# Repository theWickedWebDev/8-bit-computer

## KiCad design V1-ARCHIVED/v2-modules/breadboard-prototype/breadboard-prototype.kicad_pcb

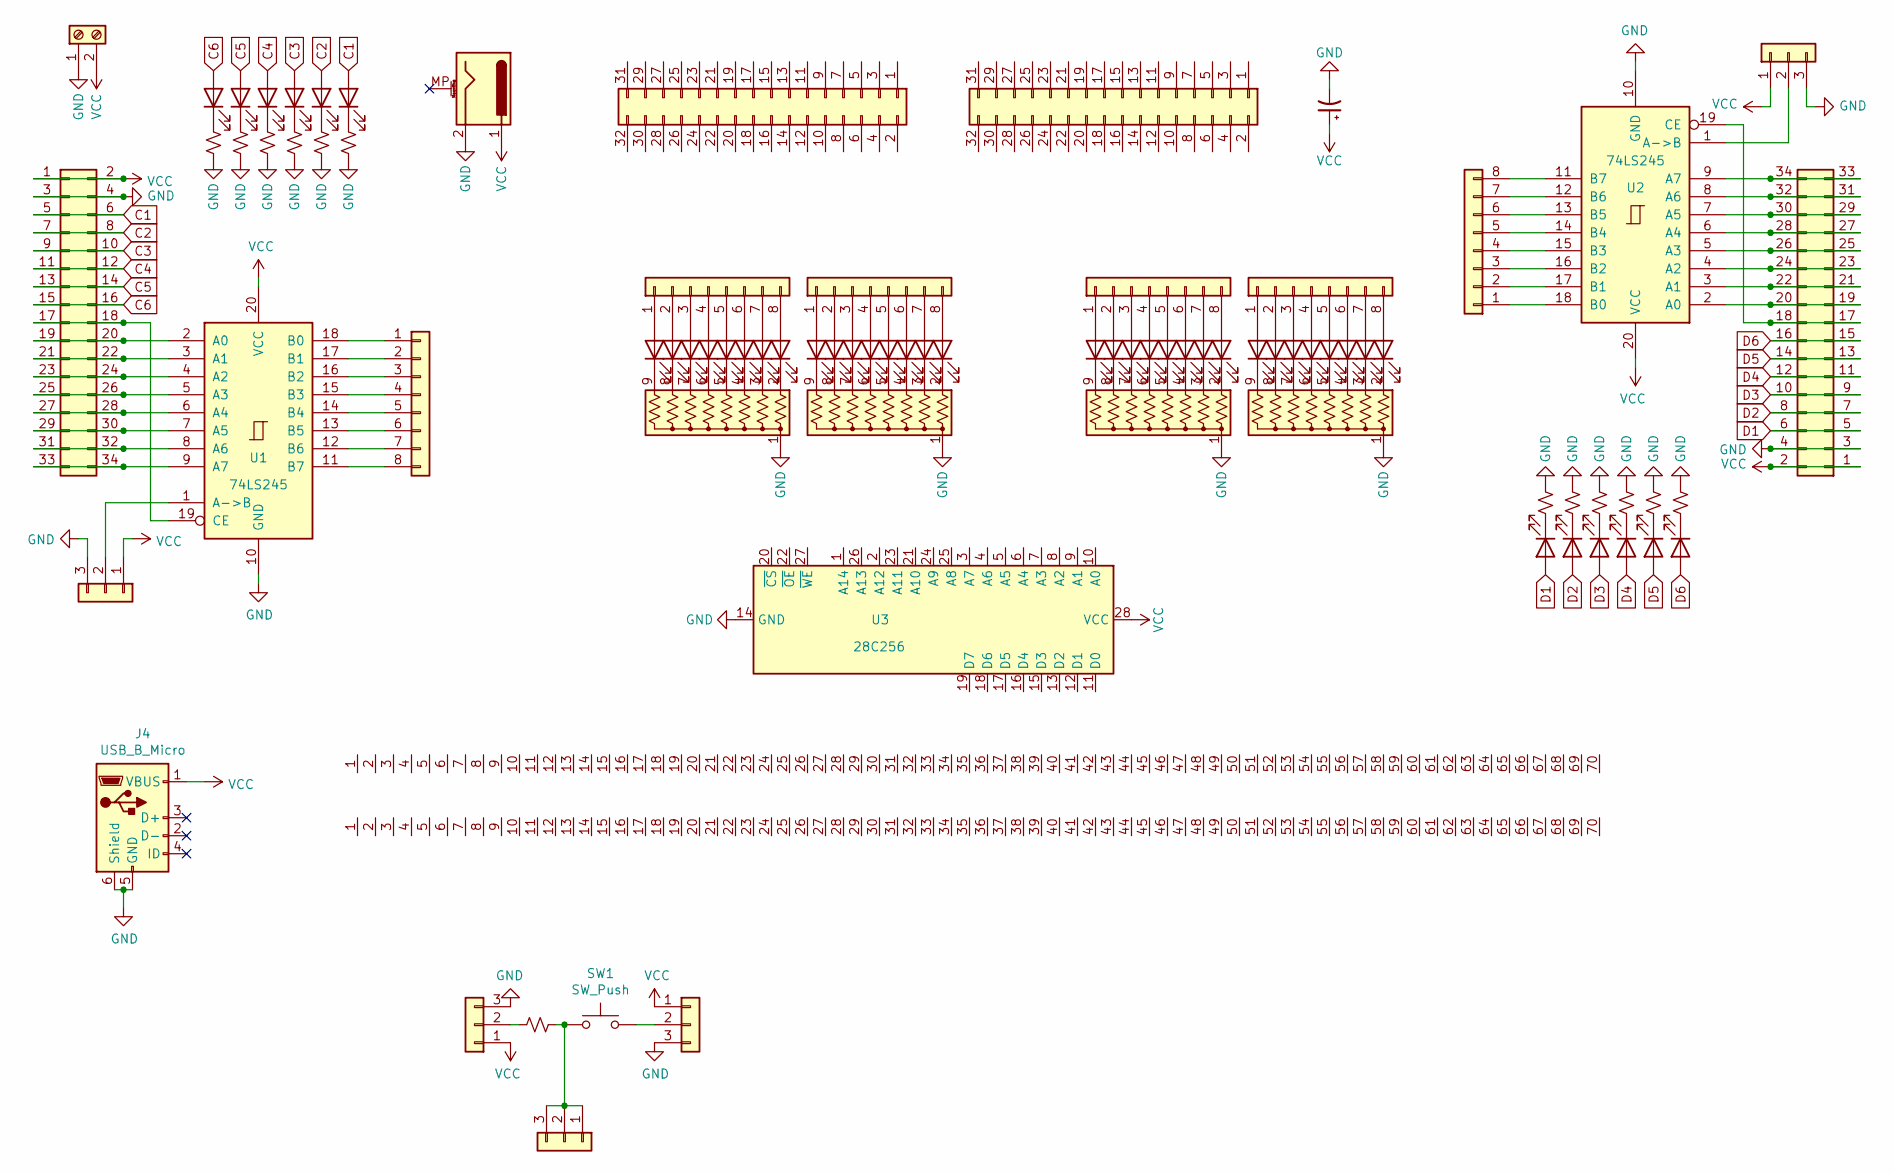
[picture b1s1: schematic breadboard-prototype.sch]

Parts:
C1: CP1_Small; CP_Radial_D8.0mm_P3.50mm
D1, D2, D3, D4, D5, D7, D8, D9, D10, D11, D12: LED; LED_0805_2012Metric
D6: LED; LED_1206_3216Metric
D13, D14, D15, D16, D17, D18, D19, D20, D21, D22, D23, D24, D25, D26, D27, D28, D29, D30, D31, D32, D33, D34, D35, D36, D37, D38, D39, D40, D41, D42, D43, D44: LED; LED_D3.0mm
J1, J6: Conn_02x17_Odd_Even; PinHeader_2x17_P2.54mm_Vertical
J2, J7, J18, J19, J20: Conn_01x03; PinHeader_1x03_P2.54mm_Vertical
J3, J8, J12, J13, J15, J16: Conn_01x08; PinHeader_1x08_P2.54mm_Vertical
J4: USB_B_Micro; USB_Micro-B_Wuerth_629105150521_CircularHoles
J5: Screw_Terminal_01x02; TerminalBlock_Phoenix_MKDS-1,5-2_1x02_P5.00mm_Horizontal
J9, J10: Conn_02x16_Odd_Even; connector_16_2
J11, J14: Conn_01x01; line_6x70
J17: Barrel_Jack_MountingPin; BarrelJack_Horizontal
R1, R2, R3, R4, R5, R6: R_Small_US; R_1206_3216Metric
R9, R10, R11, R12, R13, R14, R29: R_Small_US; R_0805_2012Metric
RN1, RN2, RN3, RN4: R_Network08_US; R_Array_SIP9
SW1: SW_Push; SW_PUSH_6mm
U1, U2: 74LS245; DIP-20_W7.62mm
U3: 28C256

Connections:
C1: D1.2 (A), J1.5, J1.6
C2: D2.2 (A), J1.7, J1.8
C3: D3.2 (A), J1.9, J1.10
C4: D4.2 (A), J1.11, J1.12
C5: D5.2 (A), J1.13, J1.14
C6: D6.2 (A), J1.15, J1.16
D1: D12.2 (A), J6.5, J6.6
D2: D11.2 (A), J6.7, J6.8
D3: D10.2 (A), J6.9, J6.10
D4: D9.2 (A), J6.11, J6.12
D5: D8.2 (A), J6.13, J6.14
D6: D7.2 (A), J6.15, J6.16
GND: C1.2, J1.3, J1.4, J2.3, J4.5 (GND), J4.6 (Shield), J5.1, J6.3, J6.4, J7.3, J17.2, J18.3, J19.3, R1.2, R2.2, R3.2, R4.2, R5.2, R6.2, R9.2, R10.2, R11.2, R12.2, R13.2, R14.2, RN1.1 (common), RN2.1 (common), RN3.1 (common), RN4.1 (common), U1.10 (GND), U2.10 (GND), U3.14 (GND)
unnamed: D1.1 (K), R1.1
unnamed: D2.1 (K), R2.1
unnamed: D3.1 (K), R3.1
unnamed: D4.1 (K), R4.1
unnamed: D5.1 (K), R5.1
unnamed: D6.1 (K), R6.1
unnamed: D7.1 (K), R9.1
unnamed: D8.1 (K), R10.1
unnamed: D9.1 (K), R11.1
unnamed: D10.1 (K), R12.1
unnamed: D11.1 (K), R13.1
unnamed: D12.1 (K), R14.1
unnamed: D13.1 (K), RN3.9 (R8)
unnamed: D13.2 (A), J12.1
unnamed: D14.1 (K), RN3.8 (R7)
unnamed: D14.2 (A), J12.2
unnamed: D15.1 (K), RN3.7 (R6)
unnamed: D15.2 (A), J12.3
unnamed: D16.1 (K), RN3.6 (R5)
unnamed: D16.2 (A), J12.4
unnamed: D17.1 (K), RN3.5 (R4)
unnamed: D17.2 (A), J12.5
unnamed: D18.1 (K), RN3.4 (R3)
unnamed: D18.2 (A), J12.6
unnamed: D19.1 (K), RN3.3 (R2)
unnamed: D19.2 (A), J12.7
unnamed: D20.1 (K), RN3.2 (R1)
unnamed: D20.2 (A), J12.8
unnamed: D21.1 (K), RN4.9 (R8)
unnamed: D21.2 (A), J13.1
unnamed: D22.1 (K), RN4.8 (R7)
unnamed: D22.2 (A), J13.2
unnamed: D23.1 (K), RN4.7 (R6)
unnamed: D23.2 (A), J13.3
unnamed: D24.1 (K), RN4.6 (R5)
unnamed: D24.2 (A), J13.4
unnamed: D25.1 (K), RN4.5 (R4)
unnamed: D25.2 (A), J13.5
unnamed: D26.1 (K), RN4.4 (R3)
unnamed: D26.2 (A), J13.6
unnamed: D27.1 (K), RN4.3 (R2)
unnamed: D27.2 (A), J13.7
unnamed: D28.1 (K), RN4.2 (R1)
unnamed: D28.2 (A), J13.8
unnamed: D29.1 (K), RN1.9 (R8)
unnamed: D29.2 (A), J15.1
unnamed: D30.1 (K), RN1.8 (R7)
unnamed: D30.2 (A), J15.2
unnamed: D31.1 (K), RN1.7 (R6)
unnamed: D31.2 (A), J15.3
unnamed: D32.1 (K), RN1.6 (R5)
unnamed: D32.2 (A), J15.4
unnamed: D33.1 (K), RN1.5 (R4)
unnamed: D33.2 (A), J15.5
unnamed: D34.1 (K), RN1.4 (R3)
unnamed: D34.2 (A), J15.6
unnamed: D35.1 (K), RN1.3 (R2)
unnamed: D35.2 (A), J15.7
unnamed: D36.1 (K), RN1.2 (R1)
unnamed: D36.2 (A), J15.8
unnamed: D37.1 (K), RN2.9 (R8)
unnamed: D37.2 (A), J16.1
unnamed: D38.1 (K), RN2.8 (R7)
unnamed: D38.2 (A), J16.2
unnamed: D39.1 (K), RN2.7 (R6)
unnamed: D39.2 (A), J16.3
unnamed: D40.1 (K), RN2.6 (R5)
unnamed: D40.2 (A), J16.4
unnamed: D41.1 (K), RN2.5 (R4)
unnamed: D41.2 (A), J16.5
unnamed: D42.1 (K), RN2.4 (R3)
unnamed: D42.2 (A), J16.6
unnamed: D43.1 (K), RN2.3 (R2)
unnamed: D43.2 (A), J16.7
unnamed: D44.1 (K), RN2.2 (R1)
unnamed: D44.2 (A), J16.8
unnamed: J1.17, J1.18, U1.19 (CE)
unnamed: J1.19, J1.20, U1.2 (A0)
unnamed: J1.21, J1.22, U1.3 (A1)
unnamed: J1.23, J1.24, U1.4 (A2)
unnamed: J1.25, J1.26, U1.5 (A3)
unnamed: J1.27, J1.28, U1.6 (A4)
unnamed: J1.29, J1.30, U1.7 (A5)
unnamed: J1.31, J1.32, U1.8 (A6)
unnamed: J1.33, J1.34, U1.9 (A7)
unnamed: J2.2, U1.1 (A->B)
unnamed: J3.1, U1.18 (B0)
unnamed: J3.2, U1.17 (B1)
unnamed: J3.3, U1.16 (B2)
unnamed: J3.4, U1.15 (B3)
unnamed: J3.5, U1.14 (B4)
unnamed: J3.6, U1.13 (B5)
unnamed: J3.7, U1.12 (B6)
unnamed: J3.8, U1.11 (B7)
unnamed: J6.17, J6.18, U2.19 (CE)
unnamed: J6.19, J6.20, U2.2 (A0)
unnamed: J6.21, J6.22, U2.3 (A1)
unnamed: J6.23, J6.24, U2.4 (A2)
unnamed: J6.25, J6.26, U2.5 (A3)
unnamed: J6.27, J6.28, U2.6 (A4)
unnamed: J6.29, J6.30, U2.7 (A5)
unnamed: J6.31, J6.32, U2.8 (A6)
unnamed: J6.33, J6.34, U2.9 (A7)
unnamed: J7.2, U2.1 (A->B)
unnamed: J8.1, U2.18 (B0)
unnamed: J8.2, U2.17 (B1)
unnamed: J8.3, U2.16 (B2)
unnamed: J8.4, U2.15 (B3)
unnamed: J8.5, U2.14 (B4)
unnamed: J8.6, U2.13 (B5)
unnamed: J8.7, U2.12 (B6)
unnamed: J8.8, U2.11 (B7)
unnamed: J18.2, R29.2
unnamed: J19.2, SW1.2
unnamed: J20.1, J20.2, J20.3, R29.1, SW1.1
VCC: C1.1, J1.1, J1.2, J2.1, J4.1 (VBUS), J5.2, J6.1, J6.2, J7.1, J17.1, J18.1, J19.1, U1.20 (VCC), U2.20 (VCC), U3.28 (VCC)

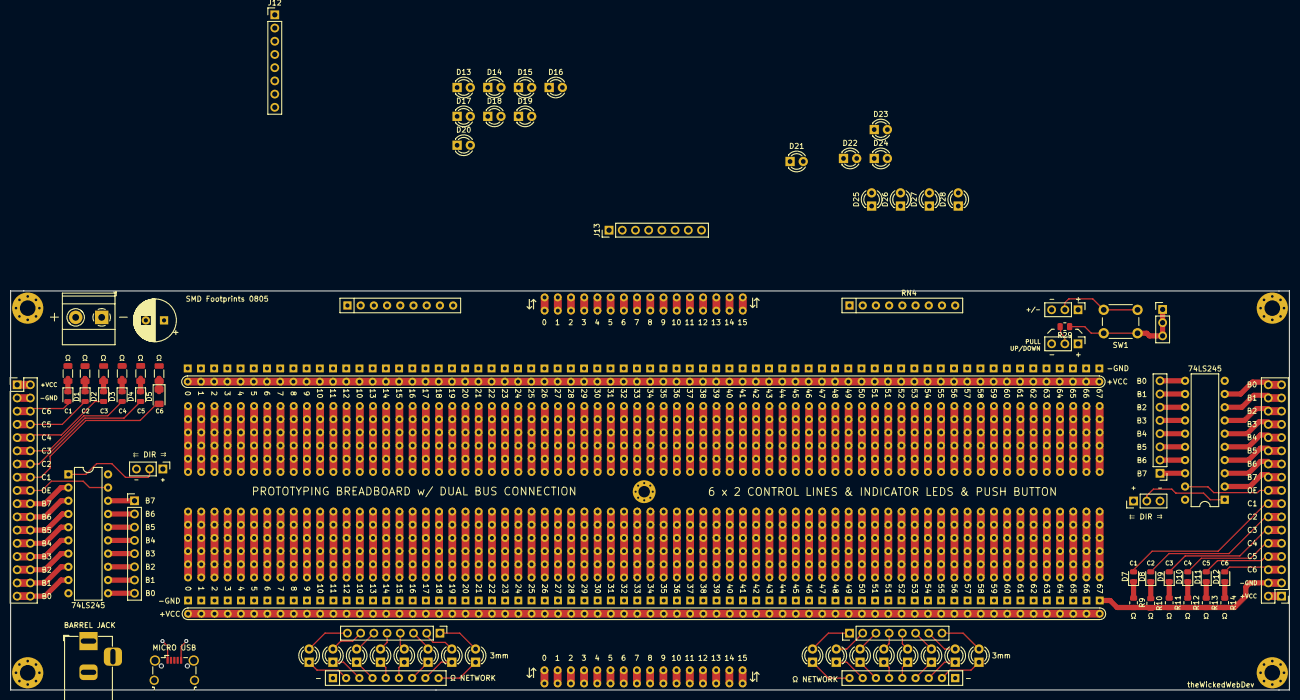
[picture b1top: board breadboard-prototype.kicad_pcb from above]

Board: 2 copper layers, 245.9 x 76.7 mm, 85 parts (0 on the bottom side), 129 nets.

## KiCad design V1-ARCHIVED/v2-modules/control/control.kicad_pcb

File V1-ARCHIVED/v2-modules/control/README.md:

# Display Module

todo fixes
- labelling is off for outputs
- invert labelling/logic is wrong

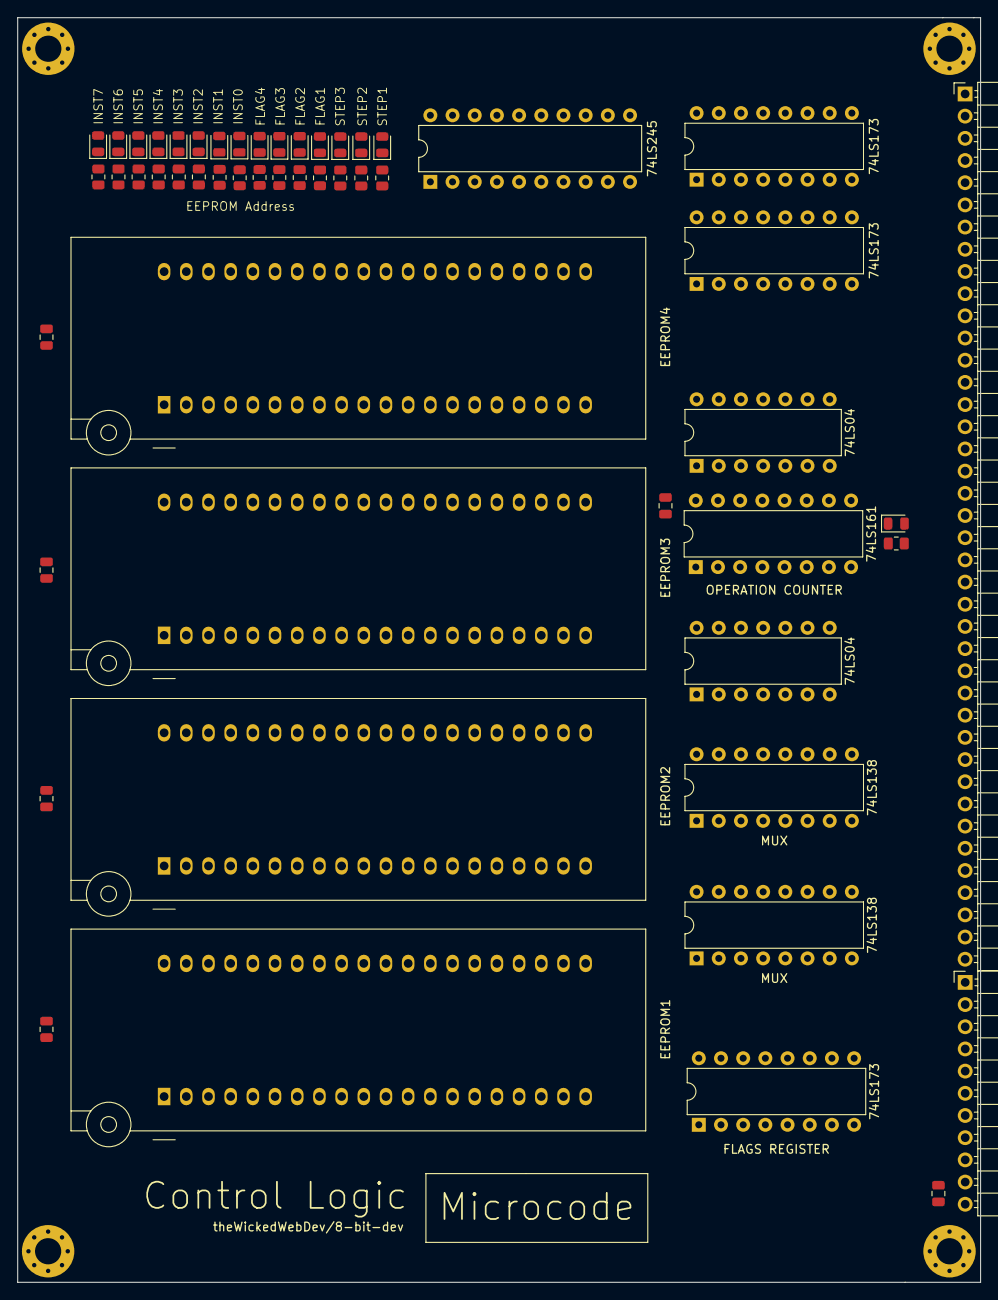
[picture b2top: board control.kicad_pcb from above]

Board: 4 copper layers, 110.2 x 144.8 mm, 53 parts (0 on the bottom side), 98 nets, no tracks yet.

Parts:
C1, C2, C3, C4, C6: CP1; C_0805_2012Metric
C5: CP_Small; C_0805_2012Metric
D1, D35, D36, D37, D38, D39, D40, D41, D42, D43, D44, D45, D46, D47, D48, D49: LED; LED_0805_2012Metric
EEPROM1, EEPROM2, EEPROM3, EEPROM4: AT28C256; EEPROM 40pin Socket
J1: Conn_01x40; PinHeader_1x40_P2.54mm_Horizontal
J2: Conn_01x11; PinHeader_1x11_P2.54mm_Horizontal
R3, R35, R36, R37, R38, R39, R40, R41, R42, R43, R44, R45, R46, R47, R48, R49: R_Small_US; R_0805_2012Metric
U1: 74LS161; DIP-16_W7.62mm
U2, U4, U5: 74LS173; DIP-16_W7.62mm
U3: 74LS245; DIP-20_W7.62mm
U6, U8: 74LS138; DIP-16_W7.62mm
U7, U10: 74LS04; DIP-14_W7.62mm

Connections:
/E1_IO0: EEPROM3.11, U10.13
/E1_IO1: EEPROM3.12, U10.11
/E1_IO2: EEPROM3.13, U10.9
/E1_IO3: EEPROM3.15, U10.5
/E1_IO4: EEPROM3.16, U10.3
/E1_IO5: EEPROM3.17, U10.1
/E2_IO0: EEPROM2.11, U8.1
/E2_IO1: EEPROM2.12, U8.2
/E2_IO2: EEPROM2.13, U8.3
/E2_IO3: EEPROM2.15, U8.6
/E2_IO4: EEPROM2.16, U6.1
/E2_IO5: EEPROM2.17, U6.2
/E2_IO6: EEPROM2.18, U6.3
/E2_IO7: EEPROM2.19, U6.6
AI: J1.19, U6.13
ALU_MODE: EEPROM1.11, J1.29
ALU_OUT: J1.34, U8.12
ALU_S0: EEPROM1.12, J1.30
ALU_S1: EEPROM1.13, J1.31
ALU_S2: EEPROM1.15, J1.32
ALU_S3: EEPROM1.16, J1.33
AO: J1.20, U8.13
BI: J1.21, U6.14
BO: J1.22, U8.14
BUS_00: J2.2, U3.11, U5.14
BUS_01: J2.3, U3.12, U5.13
BUS_02: J2.4, U3.13, U5.12
BUS_03: J2.5, U3.14, U5.11
BUS_04: J2.6, U3.15, U4.14
BUS_05: J2.7, U3.16, U4.13
BUS_06: J2.8, U3.17, U4.12
BUS_07: J2.9, U3.18, U4.11
CI: J1.23, U6.15
CLOCK: J1.36, U2.7, U4.7, U5.7
CO: J1.24, U8.15
E3_I07_UNUSED: EEPROM1.19, J1.6
E4_I03_UNUSED: EEPROM4.15, J1.1
E4_I04_UNUSED: EEPROM4.16, J1.2
E4_I05_UNUSED: EEPROM4.17, J1.3
E4_I06_UNUSED: EEPROM4.18, J1.4
E4_I07_UNUSED: EEPROM4.19, J1.5
EXTRA_INPUT_08: J1.7, U6.7
EXTRA_OUTPUT_07: J1.9, U8.9
EXTRA_OUTPUT_08: J1.8, U8.7
FLAG1: D38.2, EEPROM1.7, EEPROM2.7, EEPROM3.7, EEPROM4.7, U2.3
FLAG2: D39.2, EEPROM1.6, EEPROM2.6, EEPROM3.6, EEPROM4.6, U2.4
FLAG3: D40.2, EEPROM1.5, EEPROM2.5, EEPROM3.5, EEPROM4.5, U2.5
FLAG4: D41.2, EEPROM1.4, EEPROM2.4, EEPROM3.4, EEPROM4.4, U2.6
FLAG4_IN: J1.25, U2.11
FLAG_IN: U2.9, U2.10, U10.12
GND: C1.2, C2.2, C3.2, C4.2, C5.2, C6.2, EEPROM1.14, EEPROM1.20, EEPROM1.22, EEPROM2.14, EEPROM2.20, EEPROM2.22, EEPROM3.14, EEPROM3.20, EEPROM3.22, EEPROM4.14, EEPROM4.20, EEPROM4.22, J2.11, R3.1, R35.2, R36.2, R37.2, R38.2, R39.2, R40.2, R41.2, R42.2, R43.2, R44.2, R45.2, R46.2, R47.2, R48.2, R49.2, U1.8, U2.1, U2.2, U2.8, U3.10, U4.1, U4.2, U4.8, U5.1, U5.2, U5.8, U6.4, U6.5, U6.8, U7.7, U8.4, U8.5, U8.8, U10.7
HALT: J1.35, U10.2
INST0: D42.2, EEPROM1.3, EEPROM2.3, EEPROM3.3, EEPROM4.3, U3.9, U5.3
INST1: D43.2, EEPROM1.25, EEPROM2.25, EEPROM3.25, EEPROM4.25, U3.8, U5.4
INST2: D44.2, EEPROM1.24, EEPROM2.24, EEPROM3.24, EEPROM4.24, U3.7, U5.5
INST3: D45.2, EEPROM1.21, EEPROM2.21, EEPROM3.21, EEPROM4.21, U3.6, U5.6
INST4: D46.2, EEPROM1.23, EEPROM2.23, EEPROM3.23, EEPROM4.23, U3.5, U4.3
INST5: D47.2, EEPROM1.2, EEPROM2.2, EEPROM3.2, EEPROM4.2, U3.4, U4.4
INST6: D48.2, EEPROM1.26, EEPROM2.26, EEPROM3.26, EEPROM4.26, U3.3, U4.5
INST7: D49.2, EEPROM1.1, EEPROM2.1, EEPROM3.1, EEPROM4.1, U3.2, U4.6
INSTRUCTION_REG_IN: U4.9, U4.10, U5.9, U5.10, U10.8
INSTRUCTION_REG_OUT: U3.19, U10.6
JUMP: J1.16, U10.4
MAR1_IN: J1.38, U6.11
MAR2_IN: J1.37, U6.10
unnamed: D1.1, R3.2
unnamed: D1.2, U1.2, U7.12
unnamed: D35.1, R35.1
unnamed: D36.1, R36.1
unnamed: D37.1, R37.1
unnamed: D38.1, R38.1
unnamed: D39.1, R39.1
unnamed: D40.1, R40.1
unnamed: D41.1, R41.1
unnamed: D42.1, R42.1
unnamed: D43.1, R43.1
unnamed: D44.1, R44.1
unnamed: D45.1, R45.1
unnamed: D46.1, R46.1
unnamed: D47.1, R47.1
unnamed: D48.1, R48.1
unnamed: D49.1, R49.1
OUTPUT_IN: J1.17, U6.9
OUTPUT_SIGN: EEPROM1.17, J1.18
PROGRAM_COUNTER_ENABLE: EEPROM3.18, J1.14
PROGRAM_COUNTER_OUT: J1.15, U8.10
RAM_IN: J1.39, U6.12
RAM_OUT: J1.40, U8.11
RAM_WRITE: EEPROM1.18, J2.1
RESET: EEPROM3.19, J1.10, U2.15, U4.15, U5.15
SET_META: EEPROM4.13, J1.12
SET_TONE: EEPROM4.12, J1.11
SOUND_CONTROL_3: EEPROM4.11, J1.13
STEP1: D35.2, EEPROM1.10, EEPROM2.10, EEPROM3.10, EEPROM4.10, U1.14
STEP2: D36.2, EEPROM1.9, EEPROM2.9, EEPROM3.9, EEPROM4.9, U1.13
STEP3: D37.2, EEPROM1.8, EEPROM2.8, EEPROM3.8, EEPROM4.8, U1.12
STEP_RESET: U1.1, U10.10
VCC: C1.1, C2.1, C3.1, C4.1, C5.1, C6.1, EEPROM1.27, EEPROM1.28, EEPROM2.27, EEPROM2.28, EEPROM3.27, EEPROM3.28, EEPROM4.27, EEPROM4.28, J2.10, U1.7, U1.9, U1.10, U1.16, U2.16, U3.1, U3.20, U4.16, U5.16, U6.16, U7.14, U8.16, U10.14

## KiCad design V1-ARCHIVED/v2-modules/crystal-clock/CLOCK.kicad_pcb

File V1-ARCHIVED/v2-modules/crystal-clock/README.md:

# Clock v3.1

<br/>

KiCad Files, images and Gerber files are included.

### Description
This is a build for a computer clock module. It has two modes, `run`, which takes advantage of a *full-can quartz oscillating crystal*, and `manual`, which is a *monostable circuit* built with a *555 timer*.

## Manual (Monostable)

While in `manual mode`, the clock will pulse only when the manual button is pressed. This button is *debounced* through the 555 timer with a capacitor & resistor.

#### Formula

The formula to calculate the debounce time is:
```
1.1 * R * C
```

*ie. 1.1 * 47μf * 4KΩ = 206 (0.2 seconds)*

## Run (Astable)

This circuit continuously sends a clock pulse out. The starting frequency is the value of the `Quartz Crystal` (in my case, 1Mhz). 

The square wave from the crystal goes into the first `74LS193` Up/Down Counter. This counter is chained in series through 3 other `74LS193` counters. They are wired up to produce a single, divided-by, clock pulse.

There are 2 inputs, `A0..A7`, and `Freq. Tuning`. The data latched into `A0..A7` is sent to the 2nd, and 3rd counters, whereas the `Freq. Tuning` input is connected to the outputs of the 4th(last) counter in the series.

You can use a 2-pin jumper to chose which tuning you'd like.

<br/>
<hr/>
<br/>

## PCB Fabrication
I use www.jlcpcb.com for my circuit board manufacturing. They print 5 copies of each order. This order cost me `$9.50`

<br/>

### Schematic

<br/>

### Rendering

<br/>

<br/>

### Fritzing Breadboard
(Might not be 100% accurate)

<br/>
<hr/>
<br/>

## Parts List

### IC's
- `555` (1) - 555 Timer [Datasheet/Product](https://www.jameco.com/z/NE555P-Major-Brands-IC-LM555P-Single-Timer-LM555CN-NE555N-TL555P-MC1455P-_27422.html)

- `74LS173` (2) - 4-bit D-type Tri-state, Registers [Datasheet/Product](https://www.jameco.com/z/74LS173-Major-Brands-IC-74LS173-4-BIT-D-TYPE-REGISTER-3-STATE-OUTPUT_46922.html)

- `74LS193` (4) - Up/Down MOD-16 Binary Counter [Datasheet/Product](https://www.jameco.com/z/74LS193-Major-Brands-IC-74LS193-Synchronous-4-Bit-Up-Down-Binary-Counter_47036.html)

- `74LS08` (1) - Quad 2-input AND gate [Datasheet/Product](https://www.jameco.com/z/74LS08-Major-Brands-IC-74LS08-Quad-2-Input-Positive-AND-Gate_46375.html)

- `74LS04` (1) - HEX Inverter [Datasheet/Product](https://www.jameco.com/z/74LS04-Major-Brands-IC-74LS04-Hex-Inverter_46316.html)

- `74LS86` (1) - QUAD 2-input XOR gate [Datasheet/Product](https://www.jameco.com/z/74LS86-Major-Brands-IC-74LS86-QUAD-2-INPUT-EXCLUSIVE-OR-GATE_48098.html)

### Passive & Other
<br/>

- `1Mhz Full Can Crystal` (1) [Datasheet/Product](https://www.jameco.com/z/OSC1-Jameco-Valuepro-1-MHz-Full-Can-Crystal-Oscillator_27861.html)

- `47uf Capacitor` (1) Polarized
- `22uf Capacitor` (1) Polarized
- `100uf Capacitor` (2) Polarized (Decoupling)

- `4kΩ Resistor` (1)
- `1kΩ Resistor` (2) Pull-up Resistors
- `1.5kΩ Resistor` (2) Current limiting resistors for LEDs

- `Screw Terminal` (1) - 2pin Terminal [Datasheet/Product](https://www.jameco.com/z/EK500V-02P-R-Dinkle-Terminal-Block-Header-2-Position-Top-Screw-5mm-Solder-Straight-Thru-Hole-20A_160785.html)

- `8 Pin Switch` (1) - DIP 8-pin switch [Datasheet/Product](https://www.jameco.com/z/76SB08ST-Grayhill-DIP-Switch-On-Off-Single-Pole-Single-Throw-8-Raised-Rocker-0-15-Amp-30-Volt-PC-Pins-2000-Cycle-2-5mm-Through-Hole-Tube_696917.html)

- `Tactile SPST Button` (2) - Button [Datasheet/Product](https://www.jameco.com/z/JTP1230A-Apem-Components-Switch-Push-Button-Tactile-Single-Pole-Single-Throw-Off-Momentary-On-15-Volt-DC-20mA_1586074.html)

- `Slide SPDR Switch` (2) - SPDT 3-pin Switch [Datasheet/Product](https://www.jameco.com/z/EG218-E-Switch-Slide-Switch-SPDT-ON-ON-500mA-50VDC-3-Pin-Breadboard-Friendly_2314127.html)

- `5mm LEDs` (2)
- `3mm LEDs` (8)
- `Pin Header 1x8` (2)
- `Pin Header 1x2` (1)
- `Pin Header 2x4` (1)

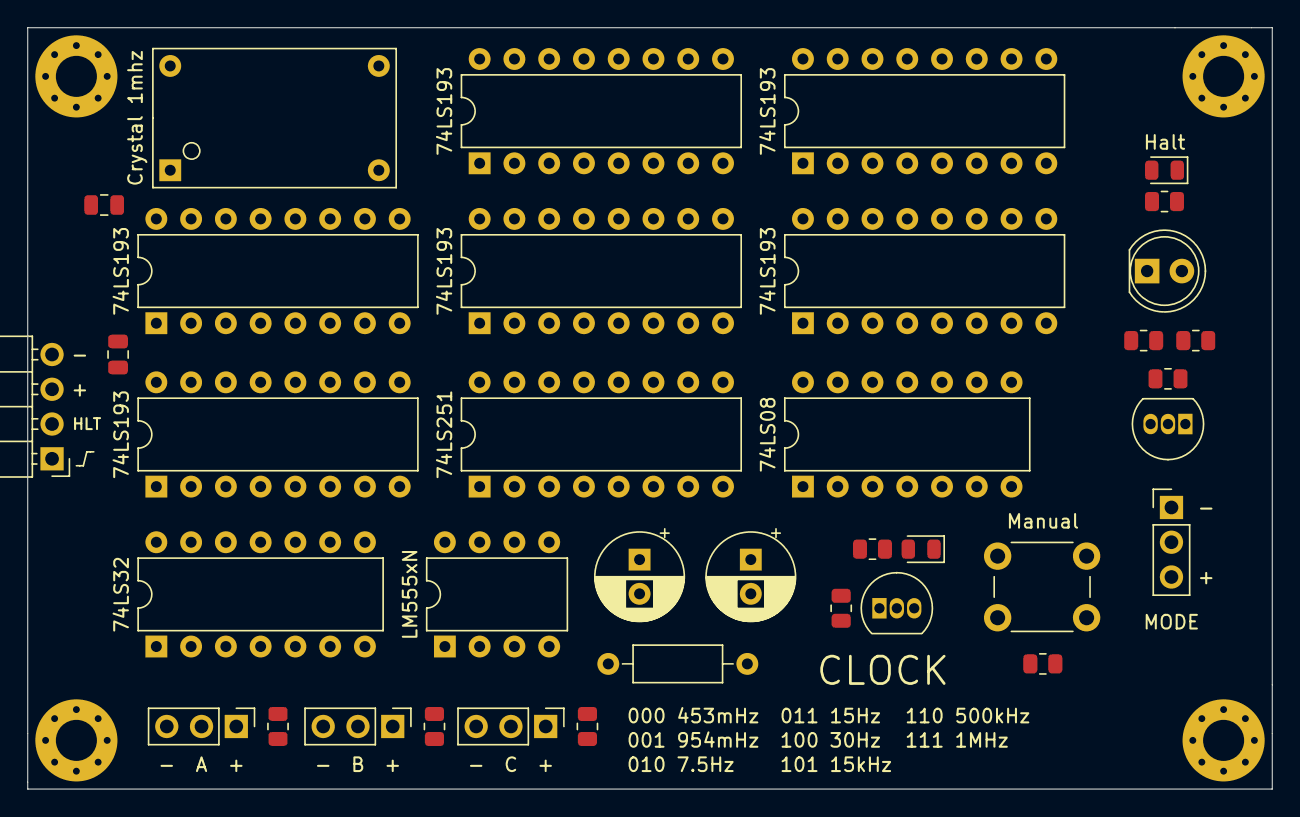
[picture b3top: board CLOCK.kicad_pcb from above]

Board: 4 copper layers, 90.9 x 55.6 mm, 37 parts (0 on the bottom side), 37 nets, no tracks yet.

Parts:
C1, C2: CP1; C_0805_2012Metric
C3, C4: CP1; CP_Radial_D6.3mm_P2.50mm
D1, D3: LED; LED_0805_2012Metric
D2: LED; LED_D5.0mm
J2: Conn_01x08; PinHeader_1x04_P2.54mm_Horizontal
J3, J5, J6, J7: Conn_01x03; PinHeader_1x03_P2.54mm_Vertical
Q1, Q2: PN2222A; TO-92_Inline
R1, R3, R4, R6, R7, R8, R9, R10, R11, R12: R_Small_US; R_0805_2012Metric
R2: R_Small_US; R_Axial_DIN0207_L6.3mm_D2.5mm_P10.16mm_Horizontal
SW3: SW_Push; SW_PUSH_6mm
U1, U2, U4, U6, U7, U8: 74LS193; DIP-16_W7.62mm
U3: 4-pin-crystal-1mhz; full-can-14pin
U5: 74LS251; DIP-16_W7.62mm
U9: 74LS08; DIP-14_W7.62mm
U10: 74LS32; DIP-14_W7.62mm
U11: LM555xN; DIP-8_W7.62mm

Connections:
1MHz_Pulse: U3.8, U4.5, U5.12
CLOCK_OUT: D2.2, J2.1, U9.8
GND: C1.2, C2.2, C3.2, C4.2, J2.4, J3.3, J5.3, J6.3, J7.1, Q1.3, Q2.3, R4.2, R6.2, R8.2, R12.2, SW3.1, U1.1, U1.8, U1.9, U1.10, U1.14, U1.15, U2.1, U2.8, U2.9, U2.10, U2.14, U2.15, U3.7, U4.1, U4.8, U4.9, U4.10, U4.14, U4.15, U5.7, U5.8, U6.1, U6.8, U6.9, U6.10, U6.14, U6.15, U7.1, U7.8, U7.9, U7.10, U7.14, U7.15, U8.1, U8.8, U8.9, U8.10, U8.14, U8.15, U9.7, U10.7, U11.1
HALT: D3.2, J2.2, Q2.2, R12.1
Monostable_Pulse: U9.5, U11.3
unnamed: C3.1, U11.5
unnamed: C4.1, R2.1, U11.6, U11.7
unnamed: D1.1, R4.1
unnamed: D1.2, J7.2, Q1.2, U9.4
unnamed: D2.1, R6.1
unnamed: D3.1, R8.1
unnamed: J3.1, R9.1
unnamed: J3.2, U5.11
unnamed: J5.1, R10.1
unnamed: J5.2, U5.10
unnamed: J6.1, R11.1
unnamed: J6.2, U5.9
unnamed: Q1.1, R1.2, U9.1
unnamed: Q2.1, R7.1, U9.9
unnamed: R3.2, SW3.2, U11.2
unnamed: U1.2, U5.14
unnamed: U1.5, U4.12
unnamed: U1.12, U2.5
unnamed: U2.12, U6.5
unnamed: U4.2, U5.13
unnamed: U5.1, U6.7
unnamed: U5.2, U7.3
unnamed: U5.3, U7.7
unnamed: U5.4, U8.3
unnamed: U5.5, U9.2
unnamed: U5.15, U6.6
unnamed: U6.12, U7.5
unnamed: U7.12, U8.5
unnamed: U9.3, U10.1
unnamed: U9.6, U10.2
unnamed: U9.10, U10.3
VCC: C1.1, C2.1, J2.3, J7.3, R1.1, R2.2, R3.1, R7.2, R9.2, R10.2, R11.2, U1.4, U1.16, U2.4, U2.16, U3.14, U4.4, U4.16, U5.16, U6.4, U6.16, U7.4, U7.16, U8.4, U8.16, U9.14, U10.14, U11.8

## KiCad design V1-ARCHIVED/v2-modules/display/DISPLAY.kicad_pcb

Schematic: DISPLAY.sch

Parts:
C16: CP1; CP_Radial_D6.3mm_P2.50mm
C133: CP; C_Disc_D6.0mm_W2.5mm_P5.00mm
C233: C; C_Disc_D6.0mm_W2.5mm_P5.00mm
J2: Conn_01x15; PinHeader_1x15_P2.54mm_Horizontal
R1, R2, R1452, R2123: R_US; R_Axial_DIN0207_L6.3mm_D2.5mm_P10.16mm_Horizontal
SW1: SW_SPST; SW_DIP_SPSTx01_Slide_9.78x4.72mm_W7.62mm_P2.54mm
U1, U4, U5, U6: HDSP-7503; 7SegmentLED_LTS6760_LTS6780
U2: 74LS08; DIP-16_W7.62mm
U3: 74LS273; DIP-20_W7.62mm
U9: AT28C256; DIP_Socket-40_W11.9_W12.7_W15.24_W17.78_W18.5_3M_240-1280-0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
U1555: NE55P; DIP-8_W7.62mm
U2444: 74LS76; DIP-16_W7.62mm
U4332: 74LS139; DIP-16_W7.62mm

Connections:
1_DISPLAY: U6.3 (CC1), U6.8 (CC2), U4332.4
10_DISPLAY: U5.3 (CC1), U5.8 (CC2), U4332.5
100_DISPLAY: U4.3 (CC1), U4.8 (CC2), U4332.6
A0: U9.25 (A8), U2444.6, U2444.14, U4332.2
A1: U9.24 (A9), U2444.10, U4332.3
A_SEG: U1.7 (A), U4.7 (A), U5.7 (A), U6.7 (A), U9.18 (IO6)
BUS0: J2.8, U3.18
BUS1: J2.9, U3.17
BUS2: J2.10, U3.14
BUS3: J2.11, U3.13
BUS4: J2.12, U3.8
BUS5: J2.13, U3.7
BUS6: J2.14, U3.4
BUS7: J2.15, U3.3
B_SEG: U1.6 (B), U4.6 (B), U5.6 (B), U6.6 (B), U9.17 (IO5)
CLOCK: J2.5, U2.2
C_SEG: U1.4 (C), U4.4 (C), U5.4 (C), U6.4 (C), U9.16 (IO4)
DP_SEG: U1.5 (DP), U4.5 (DP), U5.5 (DP), U6.5 (DP), U9.19 (IO7)
D_SEG: U1.2 (D), U4.2 (D), U5.2 (D), U6.2 (D), U9.15 (IO3)
E_SEG: U1.1 (E), U4.1 (E), U5.1 (E), U6.1 (E), U9.13 (IO2)
F_SEG: U1.9 (F), U4.9 (F), U5.9 (F), U6.9 (F), U9.12 (IO1)
GND: C16.2, C133.1, C233.2, J2.2, R1.1, R2.1, U2.7, U3.10, U9.1 (A14), U9.2 (A12), U9.14 (GND), U9.20 (~CE), U9.22 (~OE), U9.26 (A13), U1555.1, U2444.13, U4332.1, U4332.8
G_SEG: U1.10 (G), U4.10 (G), U5.10 (G), U6.10 (G), U9.11 (IO0)
HEX: J2.7, R2.2, U9.23 (A11)
unnamed: C133.2, R1452.2, U1555.2, U1555.6
unnamed: C233.1, U1555.5
unnamed: R1452.1, R2123.1, U1555.7
unnamed: U2.3, U3.11
unnamed: U3.2, U9.3 (A7)
unnamed: U3.5, U9.4 (A6)
unnamed: U3.6, U9.5 (A5)
unnamed: U3.9, U9.6 (A4)
unnamed: U3.12, U9.7 (A3)
unnamed: U3.15, U9.8 (A2)
unnamed: U3.16, U9.9 (A1)
unnamed: U3.19, U9.10 (A0)
OI: J2.6, U2.1
RATE: U1555.3, U2444.1
RST: J2.4, U3.1
SIGNED: J2.3, R1.2, SW1.2, U9.21 (A10)
SIGN_DISPLAY: U1.3 (CC1), U1.8 (CC2), U4332.7
VCC: C16.1, J2.1, R2123.2, SW1.1, U2.14, U3.20, U9.27 (~WE), U9.28 (VCC), U1555.8, U2444.2, U2444.3, U2444.4, U2444.5, U2444.7, U2444.8, U2444.9, U2444.12, U2444.16, U4332.16

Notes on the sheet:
Power
Counter
Clock
Logic Gate Power
CONNECTIONS
SEGMENT DISPLAYS
REGISTER & EEPROM

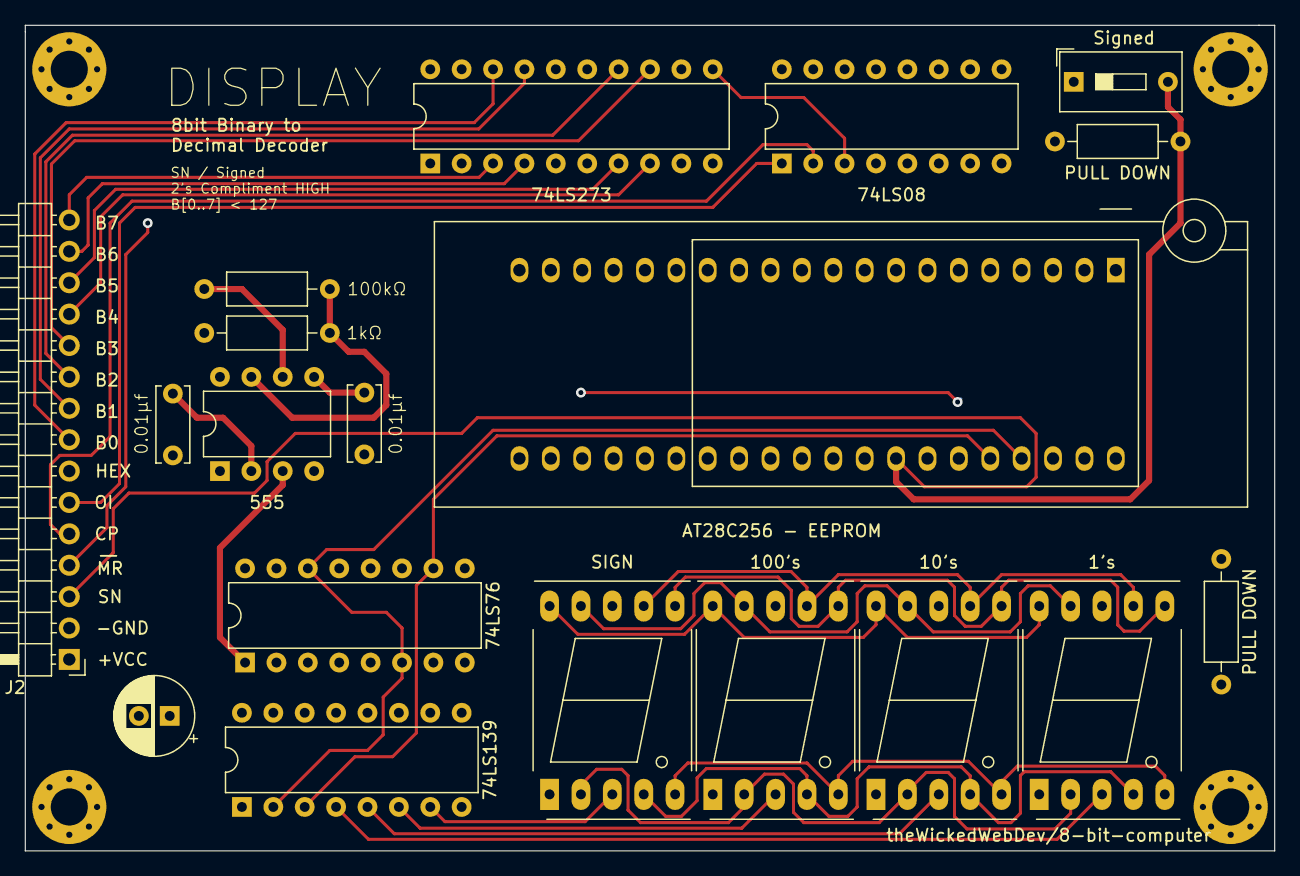
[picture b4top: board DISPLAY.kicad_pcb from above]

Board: 4 copper layers, 101.1 x 66.8 mm, 19 parts (0 on the bottom side), 42 nets.

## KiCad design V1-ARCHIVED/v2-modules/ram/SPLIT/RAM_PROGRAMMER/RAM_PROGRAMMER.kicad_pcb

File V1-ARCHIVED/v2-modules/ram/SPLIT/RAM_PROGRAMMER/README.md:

# RAM Modules

TODO: Description coming soon...

<br/>

## QA

<br/>

## PCB

<br/>

<br/>

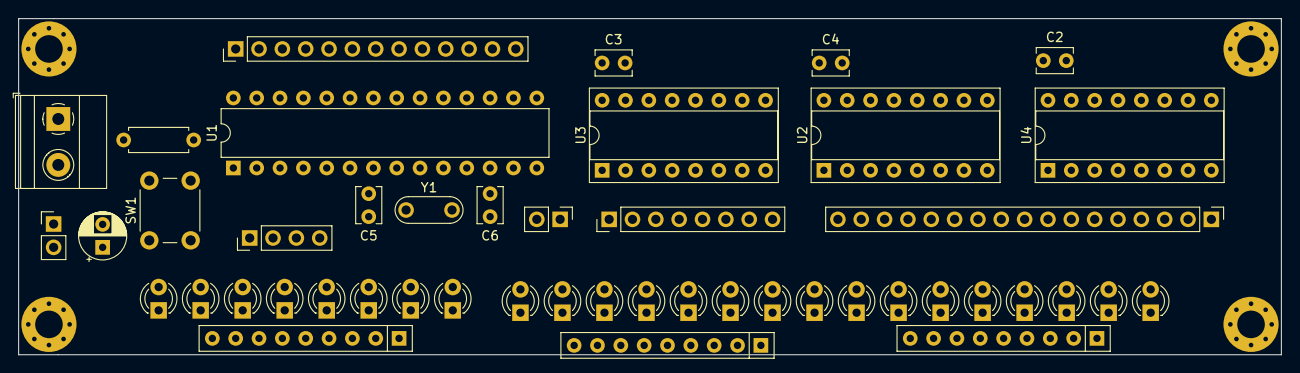
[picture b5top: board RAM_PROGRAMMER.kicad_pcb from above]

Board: 4 copper layers, 137.4 x 36.6 mm, 47 parts (0 on the bottom side), 76 nets, no tracks yet.

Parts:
C1: CP1_Small; CP_Radial_D5.0mm_P2.50mm
C2, C3, C4, C5, C6: C_Small; C_Disc_D3.8mm_W2.6mm_P2.50mm
D1, D2, D3, D4, D5, D6, D7, D8, D9, D10, D11, D12, D13, D14, D15, D16, D17, D18, D19, D20, D21, D22, D23, D24: LED; LED_D3.0mm
J1: Conn_01x17; PinHeader_1x17_P2.54mm_Vertical
J2, J3: Conn_01x02; PinHeader_1x02_P2.54mm_Vertical
J4: Screw_Terminal_01x02; TerminalBlock_Phoenix_MKDS-1,5-2_1x02_P5.00mm_Horizontal
J6: Conn_01x04; PinHeader_1x04_P2.54mm_Vertical
J7: Conn_01x08; PinHeader_1x08_P2.54mm_Vertical
J8: Conn_01x13; PinHeader_1x13_P2.54mm_Vertical
R1: R_Small_US; R_Axial_DIN0207_L6.3mm_D2.5mm_P7.62mm_Horizontal
RN1, RN2, RN3: R_Network08_US; R_Array_SIP9
SW1: SW_Push; SW_PUSH_6mm
U1: ATmega328-PU; DIP-28_W7.62mm
U2, U4: 74LS32; DIP-16_W7.62mm_Socket
U3: 74HC595; DIP-16_W7.62mm_Socket
Y1: Crystal; Resonator-2Pin_W7.0mm_H2.5mm

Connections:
/SH_CLK: U1.5, U2.11, U3.11, U4.11
/SH_DATA: U1.4, U3.14
/SH_LATCH: U1.6, U2.12, U3.12, U4.12
/SH_OE: U1.11, U2.13, U3.13, U4.13
A0: D23.2, J1.1, U4.7
A1: D21.2, J1.2, U4.6
A2: D19.2, J1.3, U4.5
A3: D17.2, J1.4, U4.4
A4: D15.2, J1.5, U4.3
A5: D13.2, J1.6, U4.2
A6: D11.2, J1.7, U4.1
A7: D9.2, J1.8, U4.15
A8: D8.2, J1.9, U2.7
A9: D7.2, J1.10, U2.6
A10: D6.2, J1.11, U2.5
A11: D5.2, J1.12, U2.4
A12: D4.2, J1.13, U2.3
A13: D3.2, J1.14, U2.2
A14: D2.2, J1.15, U2.1
A15: D1.2, J1.16, U2.15
ACTIVE: J2.1, U1.13
AREF: J8.1, U1.21
D0: D24.2, J7.8, U3.7
D1: D22.2, J7.7, U3.6
D2: D20.2, J7.6, U3.5
D3: D18.2, J7.5, U3.4
D4: D16.2, J7.4, U3.3
D5: D14.2, J7.3, U3.2
D6: D12.2, J7.2, U3.1
D7: D10.2, J7.1, U3.15
GND: C1.2, C2.2, C3.2, C4.2, C5.1, C6.1, J1.17, J3.1, J4.1, J6.4, RN1.1, RN2.1, RN3.1, SW1.1, U1.8, U1.22, U2.8, U3.8, U4.8
unnamed: C5.2, U1.9, Y1.1
unnamed: C6.2, U1.10, Y1.2
unnamed: D1.1, RN1.9
unnamed: D2.1, RN1.8
unnamed: D3.1, RN1.7
unnamed: D4.1, RN1.6
unnamed: D5.1, RN1.5
unnamed: D6.1, RN1.4
unnamed: D7.1, RN1.3
unnamed: D8.1, RN1.2
unnamed: D9.1, RN2.9
unnamed: D10.1, RN3.9
unnamed: D11.1, RN2.8
unnamed: D12.1, RN3.8
unnamed: D13.1, RN2.7
unnamed: D14.1, RN3.7
unnamed: D15.1, RN2.6
unnamed: D16.1, RN3.6
unnamed: D17.1, RN2.5
unnamed: D18.1, RN3.5
unnamed: D19.1, RN2.4
unnamed: D20.1, RN3.4
unnamed: D21.1, RN2.3
unnamed: D22.1, RN3.3
unnamed: D23.1, RN2.2
unnamed: D24.1, RN3.2
unnamed: U2.9, U4.14
unnamed: U2.14, U3.9
PB0: J8.13, U1.14
PB1: J8.12, U1.15
PB2: J8.11, U1.16
PB3: J8.10, U1.17
PB4: J8.9, U1.18
PB5: J8.8, U1.19
PC0: J8.7, U1.23
PC1: J8.6, U1.24
PC2: J8.5, U1.25
PC3: J8.4, U1.26
PC4: J8.3, U1.27
PC5: J8.2, U1.28
RESET: J6.3, R1.2, SW1.2, U1.1
RX: J6.1, U1.2
TX: J6.2, U1.3
VCC: C1.1, C2.1, C3.1, C4.1, J3.2, J4.2, R1.1, U1.7, U1.20, U2.10, U2.16, U3.10, U3.16, U4.10, U4.16
WRITE_ENABLE: J2.2, U1.12
